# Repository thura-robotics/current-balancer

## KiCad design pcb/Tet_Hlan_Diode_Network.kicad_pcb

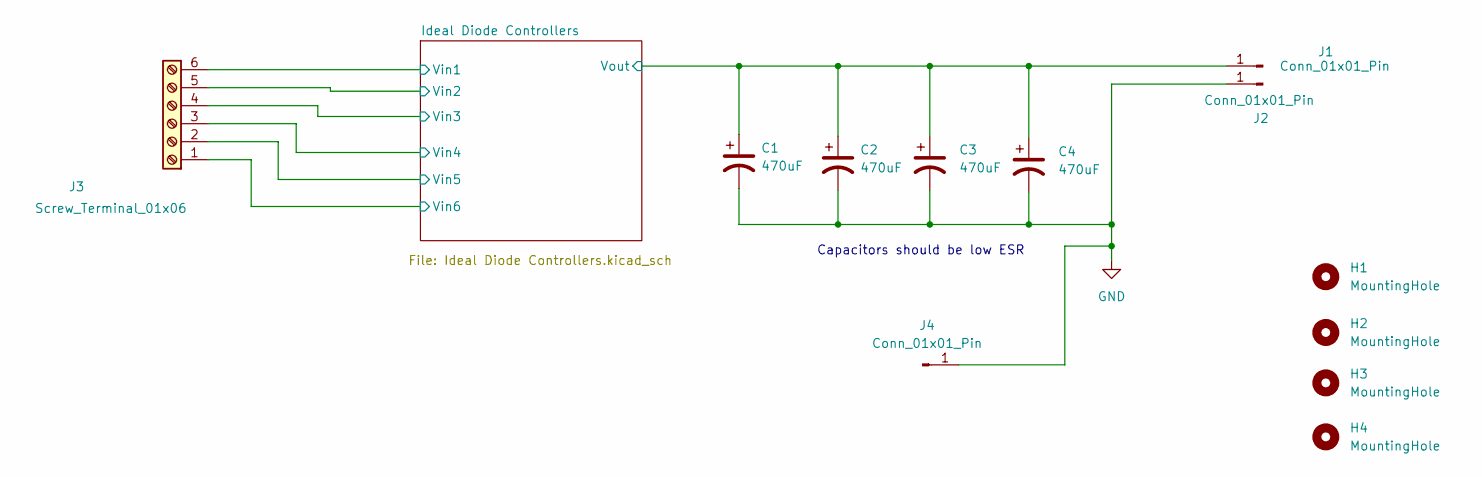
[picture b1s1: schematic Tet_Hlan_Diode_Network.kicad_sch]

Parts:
C1, C2, C3, C4: 470uF; CP_Radial_D16.0mm_P7.50mm
H1, H2, H3, H4: MountingHole; MountingHole_3mm
J1, J2, J4: Conn_01x01_Pin; XFCN T44007
J3: Screw_Terminal_01x06; TerminalBlock_Dinkle_DT-55-B01X-06_P10.00mm

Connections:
/Ideal Diode Controllers/S1: J3.6; also elsewhere on the board
/Ideal Diode Controllers/S2: J3.5; also elsewhere on the board
/Ideal Diode Controllers/S3: J3.4; also elsewhere on the board
/Ideal Diode Controllers/S4: J3.3; also elsewhere on the board
/Ideal Diode Controllers/S5: J3.2; also elsewhere on the board
/Ideal Diode Controllers/S6: J3.1; also elsewhere on the board
/Ideal Diode Controllers/Vout: C1.1, C2.1, C3.1, C4.1, J1.1; also elsewhere on the board
GND: C1.2, C2.2, C3.2, C4.2, J2.1, J4.1; also elsewhere on the board

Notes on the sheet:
Capacitors should be low ESR

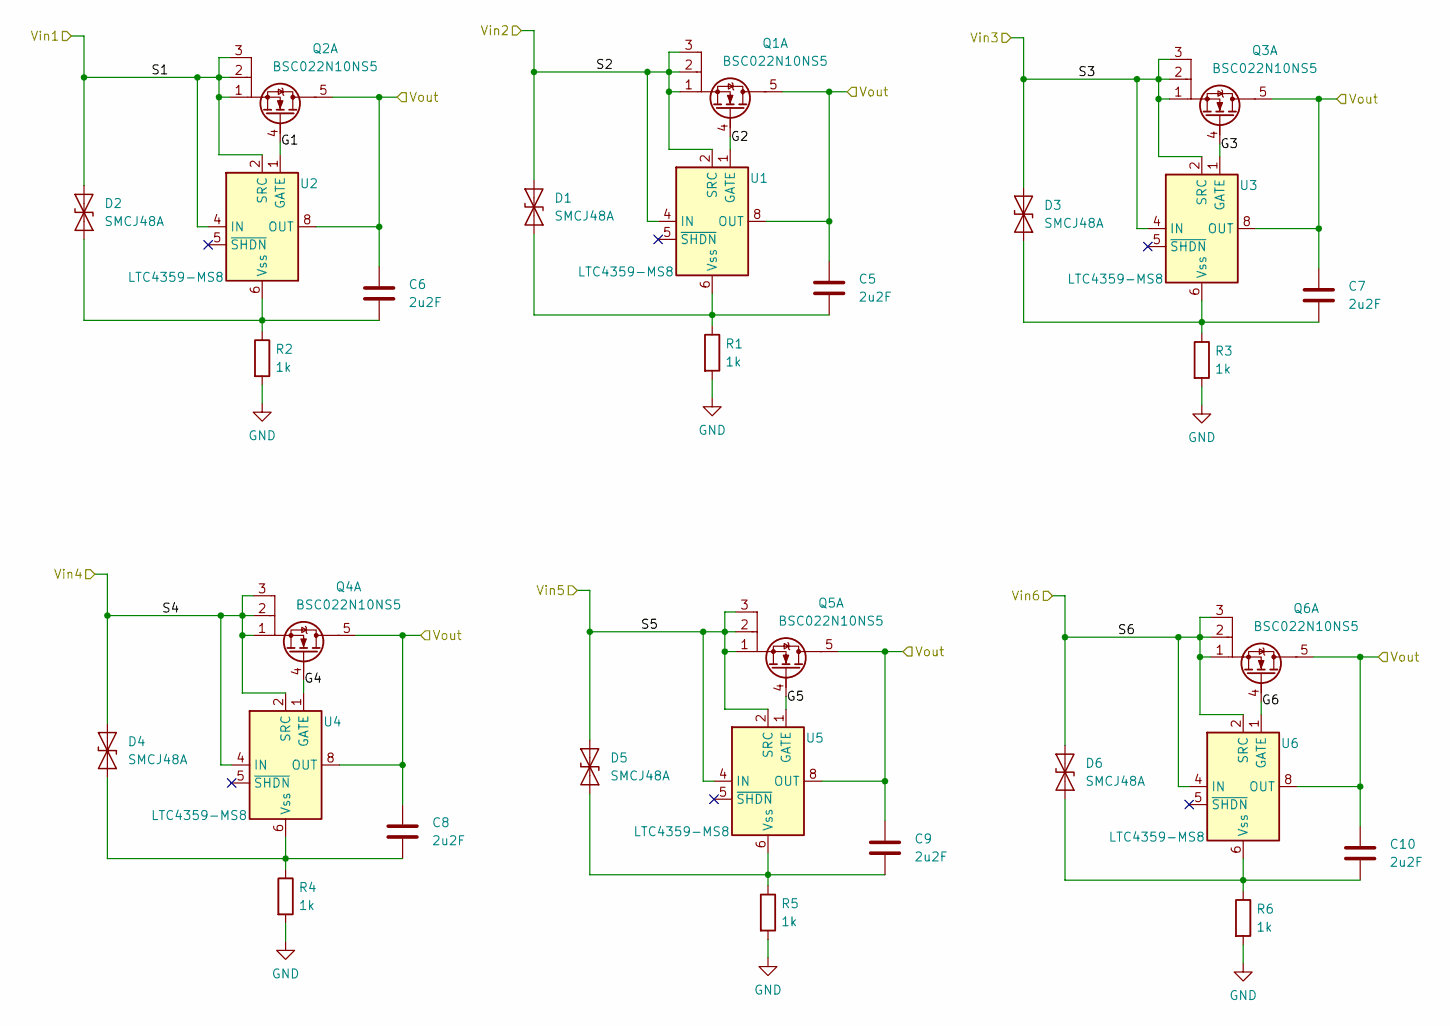
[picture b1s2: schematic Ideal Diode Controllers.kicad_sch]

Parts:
C5, C6, C7, C8, C9, C10: 2u2F; C_1210_3225Metric_Pad1.33x2.70mm_HandSolder
D1, D2, D3, D4, D5, D6: SMCJ48A; D_SMA
Q1, Q2, Q3, Q4, Q5, Q6: BSC022N10NS5; Infineon_PG-TDSON-8_6.15x5.15mm
R1, R2, R3, R4, R5, R6: 1k; R_1206_3216Metric_Pad1.30x1.75mm_HandSolder
U1, U2, U3, U4, U5, U6: LTC4359-MS8; MSOP-8_3x3mm_P0.65mm

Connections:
/Ideal Diode Controllers/G1: Q2.4 (S1), U2.1 (GATE)
/Ideal Diode Controllers/G2: Q1.4 (S1), U1.1 (GATE)
/Ideal Diode Controllers/G3: Q3.4 (S1), U3.1 (GATE)
/Ideal Diode Controllers/G4: Q4.4 (S1), U4.1 (GATE)
/Ideal Diode Controllers/G5: Q5.4 (S1), U5.1 (GATE)
/Ideal Diode Controllers/G6: Q6.4 (S1), U6.1 (GATE)
/Ideal Diode Controllers/S1: D2.2 (A2), Q2.1 (G1), Q2.2 (G1), Q2.3 (G1), U2.2 (SRC), U2.4 (IN); also elsewhere on the board
/Ideal Diode Controllers/S2: D1.2 (A2), Q1.1 (G1), Q1.2 (G1), Q1.3 (G1), U1.2 (SRC), U1.4 (IN); also elsewhere on the board
/Ideal Diode Controllers/S3: D3.2 (A2), Q3.1 (G1), Q3.2 (G1), Q3.3 (G1), U3.2 (SRC), U3.4 (IN); also elsewhere on the board
/Ideal Diode Controllers/S4: D4.2 (A2), Q4.1 (G1), Q4.2 (G1), Q4.3 (G1), U4.2 (SRC), U4.4 (IN); also elsewhere on the board
/Ideal Diode Controllers/S5: D5.2 (A2), Q5.1 (G1), Q5.2 (G1), Q5.3 (G1), U5.2 (SRC), U5.4 (IN); also elsewhere on the board
/Ideal Diode Controllers/S6: D6.2 (A2), Q6.1 (G1), Q6.2 (G1), Q6.3 (G1), U6.2 (SRC), U6.4 (IN); also elsewhere on the board
/Ideal Diode Controllers/Vout: C5.1, C6.1, C7.1, C8.1, C9.1, C10.1, Q1.5 (D1), Q2.5 (D1), Q3.5 (D1), Q4.5 (D1), Q5.5 (D1), Q6.5 (D1), U1.8 (OUT), U2.8 (OUT), U3.8 (OUT), U4.8 (OUT), U5.8 (OUT), U6.8 (OUT); also elsewhere on the board
GND: R1.2, R2.2, R3.2, R4.2, R5.2, R6.2; also elsewhere on the board
unnamed: C5.2, D1.1 (A1), R1.1, U1.6 (Vss)
unnamed: C6.2, D2.1 (A1), R2.1, U2.6 (Vss)
unnamed: C7.2, D3.1 (A1), R3.1, U3.6 (Vss)
unnamed: C8.2, D4.1 (A1), R4.1, U4.6 (Vss)
unnamed: C9.2, D5.1 (A1), R5.1, U5.6 (Vss)
unnamed: C10.2, D6.1 (A1), R6.1, U6.6 (Vss)

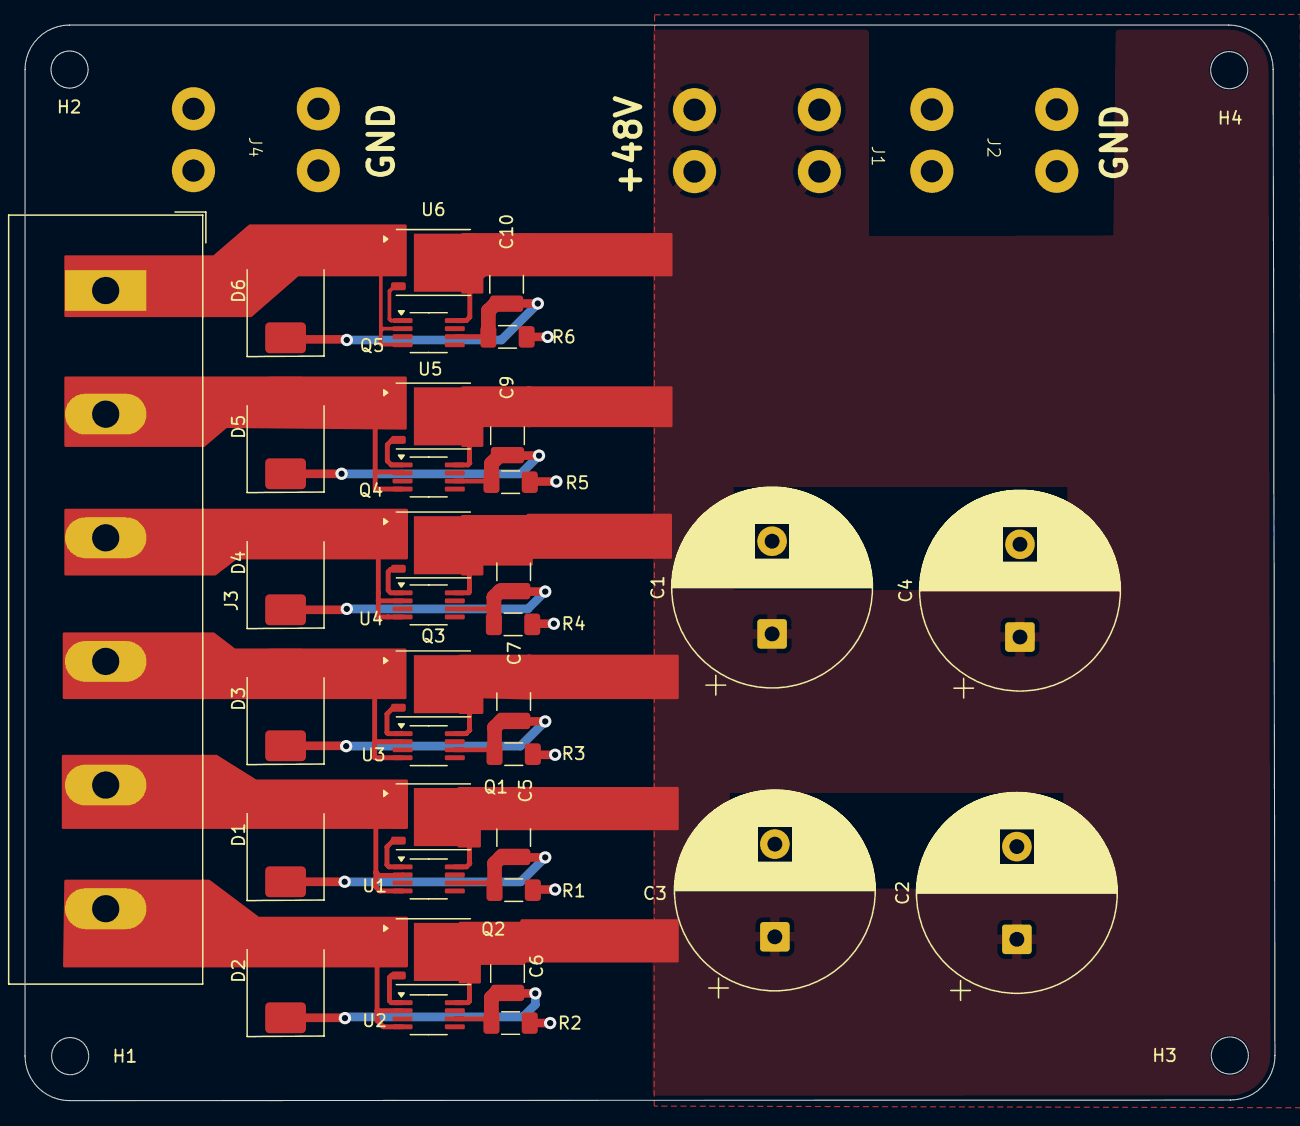
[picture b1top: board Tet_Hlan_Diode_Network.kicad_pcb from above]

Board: 2 copper layers, 101.1 x 87.0 mm, 42 parts (0 on the bottom side), 20 nets.

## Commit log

2026-05-20 Rename STM32F4_LineFollower.glb to Tet_Hlan_Diode_Network.glb
2026-05-20 Replace the new GLB file
